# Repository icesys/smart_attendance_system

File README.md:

<h1 align="center">Smart Attendance System</h1>

<p align="center">
  
  <br>
  <sub><i>The finished device: three stacked PCBs.</i></sub>
</p>

<p align="center">
  <b>Embedded systems project</b><br>
  A battery-powered, cable-free device that records lecture attendance when students tap their existing RFID student card.
</p>

<p align="center">
  <a href="#-about">About</a> &nbsp;·&nbsp;
  <a href="#-from-prototype-to-final-device">Build</a> &nbsp;·&nbsp;
  <a href="#-how-it-works">How It Works</a> &nbsp;·&nbsp;
  <a href="#-key-features">Features</a> &nbsp;·&nbsp;
  <a href="#-hardware">Hardware</a> &nbsp;·&nbsp;
  <a href="#-pinout">Pinout</a> &nbsp;·&nbsp;
  <a href="#-firmware">Firmware</a> &nbsp;·&nbsp;
  <a href="#-documentation">Documentation</a> &nbsp;·&nbsp;
  <a href="#-repository-structure">Structure</a> &nbsp;·&nbsp;
  <a href="#-roadmap">Roadmap</a>
</p>

---

<h2>📌 About</h2>

Attendance in lecture halls is still often taken on a sheet of paper. That wastes time, invites mistakes and fraud (signing for an absent friend), and the data has to be typed in again afterwards.

Every student already carries a **student card with an RFID chip**, used daily at the student restaurant: you lay it flat on a small reader and the visit is recorded. We (**Evidence Tsongodza** and **Langelihle Sasha Mandebvu**) built **Smart Attendance System** to bring the same gesture to lectures. At the end of the session the lecturer stands at the door with the device, and each student taps their card on the way out. The device identifies the student, time-stamps the tap, ignores repeated taps and saves everything to a microSD card. Afterwards the lecturer plugs it into a PC, where the card appears as a **USB drive** holding ready-to-use CSV files.

> [!NOTE]
> Status: **complete.** The three PCBs are built and assembled, and the device passed all eight system tests (T1 to T8).

---

<h2>📸 From Prototype to Final Device</h2>

<table>
  <tr>
    <td align="center" width="50%"><br><b>Breadboard prototype</b></td>
    <td align="center" width="50%"><br><b>Final device reading a card</b></td>
  </tr>
</table>

---

<h2>🔄 How It Works</h2>

1. The lecturer switches the device on (the blue LED blinks twice every 3 s) and presses **button 1** to start a session.
2. Each student lays their card flat on the **TAP CARD** area (125 kHz field).
3. The RDM6300 reader sends the card UID to the ESP32-S3, which checks the frame, looks the UID up in `students.csv`, reads the time from the DS3231 clock and appends a line to the session file.
4. LEDs, buzzer and OLED show the result straight away: **present**, **unknown card**, **duplicate** or **error**.
5. A long press on button 1 ends the session and writes a final list sorted by surname.
6. After the lecture, plugging the native USB-C port into a PC shows the microSD card as a USB drive.

No cable is needed during the lecture: the device runs on an 18650 battery charged over USB-C.

---

<h2>⚡ Key Features</h2>

| | Feature | Detail |
|---|---|---|
| 🧠 | **Controller** | ESP32-S3 N16R8 dev board (16 MB flash, 8 MB PSRAM, native USB) |
| 💳 | **Card reading** | RDM6300, 125 kHz EM4100, card laid flat, 14-byte frame checked by XOR checksum |
| 🕒 | **Time stamps** | DS3231 real-time clock with CR2032 backup |
| 💾 | **Storage** | microSD (FAT32): one CSV per session + a sorted final list per session |
| 🖥️ | **PC access** | USB drive mode (automatic when a PC is plugged in) + serial commands |
| 🔁 | **No duplicates** | A card is counted once per session; a card left on the reader is ignored for 1.5 s |
| 👤 | **Student list** | `students.csv` maps each UID to surname, first names and registration number |
| 🔔 | **Feedback** | 3 LEDs, buzzer (transistor driven), 0.96" OLED |
| 🔋 | **Power** | 18650 cell → TP4056 (USB-C charging + protection) → switch → MT3608 5 V boost |
| 🛠️ | **PCBs** | Three stacked 95 × 60 mm two-layer boards designed in KiCad, joined by two ribbon cables |

---

<h2>💳 Why a 125 kHz Reader?</h2>

The frequency of the student card was not documented. An iPhone (NFC Tools) and an Android phone did not detect the card, while the same Android phone read a passport (13.56 MHz) normally. Phones only read 13.56 MHz, so the card is low frequency (**125 kHz**). The RDM6300 reader then confirmed it.

<h2>🔬 Why ESP32-S3?</h2>

Its **native USB** lets the microSD card appear as a USB drive on the PC with no software to install. It also has enough pins, memory and speed for the reader, clock, card, display and feedback at once. The **dev board is mounted on sockets** instead of designing around the bare chip, which avoids the riskiest part of the board design (antenna, flash, boot circuit).

---

<h2>🏗️ System Architecture</h2>

```mermaid
flowchart LR
    CARD[Student card 125 kHz] -.->|field| COIL[Antenna coil]
    COIL --> RFID[RDM6300 reader]
    RFID -->|UART 9600| MCU[ESP32-S3]
    BTN[2 buttons] -->|GPIO40/41| MCU
    RTC[DS3231 clock] <-->|I2C| MCU
    MCU <-->|SPI| SD[(microSD)]
    MCU -->|I2C| OLED[OLED 0.96in]
    MCU -->|GPIO1/2/5, 42| FB[3 LEDs + buzzer]
    MCU <-->|native USB-C| PC[Lecturer's PC]
    BAT[18650] --> CHG[TP4056] --> SW[Switch] --> BOOST[MT3608 5 V] --> D[Schottky] -->|5V_SYS| MCU
```

---

<h2>🔧 Hardware</h2>

The circuit is split over **three stacked 95 × 60 mm boards** to keep the device hand-sized:

| Board | Contents |
|---|---|
| **TOP** | OLED, blue/green/red LEDs, 2 buttons, buzzer + 2N2222A, RFID coil area (no copper) |
| **MIDDLE** | ESP32-S3 on 2 × 22 sockets, RDM6300, Schottky diode, decoupling |
| **BOTTOM** | 18650 holder (underneath), TP4056, slide switch, MT3608, 470 µF, microSD, DS3231 |

Cable 1 joins TOP J1 ↔ MIDDLE J105; cable 2 joins MIDDLE J106 ↔ BOTTOM J201. Both are 16-wire ribbons with the same pin number at both ends.

**Power path:** 18650 → TP4056 → switch → MT3608 (set to **5.0 V with a multimeter before connecting anything**) → Schottky → 5V_SYS (ESP32 5V pin, RDM6300, microSD). 3V3 comes from the ESP32 board regulator (OLED, DS3231, LEDs, buzzer).

> [!WARNING]
> On the protected TP4056, **B− is not ground**: it sits behind the protection transistors. The system ground is **OUT−**. Remove the charging resistor of the DS3231 module: the CR2032 is not rechargeable.

**KiCad projects** (all in `hardware/schematics/kicad/`):

| Project | What it is |
|---|---|
| `sas_complete/` | **The whole system as one circuit**: modules as named-pin blocks, no board connectors (A3) |
| `sas_full_system/` | The three boards and both ribbon cables on one A1 sheet |
| `sas_schematics/` | One sheet per board (hierarchical), shared symbol and footprint libraries |
| `sas_pcb/` | The three routed PCBs, BOM, connector table, power notes, 1:1 printouts |

Gerber and drill files for manufacturing are in `hardware/gerbers/` (one folder per board; zip each folder to upload it). The schematic nets match the routed PCBs (29 nets, identical). Datasheets of every chip and module are in `hardware/datasheets/`.

---

<h2>🔌 Pinout</h2>

| ESP32-S3 GPIO | Connected to | Bus |
|---|---|---|
| 1 / 2 / 5 | Green / red / blue LED (220 Ω) | output |
| 42 | Buzzer transistor base (1 kΩ) | output |
| 40 / 41 | Button 1 (session) / button 2 (info) | input, pull-up |
| 8 / 9 | SCL / SDA: OLED 0x3C, DS3231 0x68 | I2C |
| 10 / 11 / 12 / 13 | microSD CS / SCK / MOSI / MISO | SPI |
| 18 | RDM6300 TX | UART1, 9600 baud |

All pins and options live in [`firmware/include/config.h`](firmware/include/config.h).

---

<h2>🎯 Device Feedback</h2>

| Event | LED | Buzzer |
|---|---|---|
| Start-up OK | green × 3 | 3 beeps |
| Student present | green | 1 short beep |
| Unknown card | red | 1 long beep |
| Duplicate tap | red × 2 | 2 beeps |
| No session running | red × 2 | 2 beeps |
| Session started / ended | green × 3 / red × 2 (long) | 3 beeps / 2 long beeps |
| Error (SD card, clock) | red × 3 | 3 beeps |
| System on | blue: 2 blinks every 3 s | — |

---

<h2>💾 Firmware</h2>

PlatformIO project (Arduino framework) in [`firmware/`](firmware/):

| File | Content |
|---|---|
| `src/main.cpp` | Main program: sessions, card handling, LED/buzzer patterns, OLED, USB drive mode, serial commands |
| `include/config.h` | Every pin, timing and option in one place |
| `include/parsers.h` | Plain C++ helpers (RDM6300 frames, CSV lines, sorting), testable on a PC |
| `test/host/test_parsers.cpp` | 26 unit tests for `parsers.h` (run on the PC) |
| `sketches/D1 … D9` | Step-by-step hardware tests: serial, I2C scan, clock, microSD, reader, LEDs/buzzer/buttons, card read, OLED, clock diagnosis |
| `tools/set_clock.py` | Sets the DS3231 to the PC time over the serial port |
| `data/students.csv` | Template of the student list to copy to the microSD card |

**Files on the microSD card**

| Path | Content |
|---|---|
| `/students.csv` | `UID,Surname,Names,Matricule`, one student per line |
| `/attendance/YYYYMMDD_hhmmss.csv` | One file per session: `uid,surname,names,matricule,date,time,result` |
| `/final/YYYYMMDD_hhmmss.txt` | Final list of the session, sorted by surname, tab-separated (paste into Excel) |

**Build and flash**

```bash
cd firmware
pio run                # build (env: esp32-s3-n16r8)
pio run -t upload      # flash
pio device monitor     # serial monitor, 115200 baud, then type HELP
g++ -std=c++17 -Iinclude test/host/test_parsers.cpp -o t && ./t    # unit tests on the PC
```

<details>
<summary><b>Serial commands</b></summary>
<br>

| Command | Action |
|---|---|
| `HELP` | List the commands |
| `STATUS` | Clock, SD card, students, session |
| `TIME` / `SETTIME YYYY-MM-DD HH:MM:SS` | Show / set the clock |
| `START` / `STOP` | Start or stop a session |
| `LIST`, `DUMP <file>` | List the files / print one |
| `FINAL [file]` | Build and show the sorted final list |
| `STUDENTS`, `RELOAD` | Show / reload the student list |
| `INIT` | Restart the SD card after a problem |
| `MUTE` | Mute or unmute the buzzer |
| `DRIVE` | Show the SD card as a USB drive now |
| `INFO` | Time and count of the last file (same as button 2) |
| `REBOOT` | Restart (also leaves drive mode) |

</details>

<details>
<summary><b>Upload notes</b></summary>
<br>

- Drive mode uses the **native** USB-C port (TinyUSB); serial output goes to the **UART** USB-C port.
- If upload fails with "Unable to verify flash chip connection", hold **BOOT** while it says `Connecting...`.
- On Linux, if the port is not found, add your user to the `dialout` group.

</details>

---

<h2>📚 Documentation</h2>

| Document | Content |
|---|---|
| [`documentation/rapport_final/`](documentation/rapport_final/) | **Project report** in French and English (Word + PDF) |
| [`documentation/poster/`](documentation/poster/) | **Exhibition poster**, two A0 sheets joined side by side (French) |
| `documentation/Resume_mini_projet_smart_attendance_system.pdf` | Short project summary (French) |
| `documentation/bill_of_materials.md` | All parts, grouped by function, with board references |
| `documentation/assembly_guide.md` | PCB soldering order, stacking and first power-on |
| `documentation/system_architecture.md` | Blocks, power rails, data flow |
| `documentation/requirements.md`, `decisions_log.md`, `test_plan.md`, `project_plan.md` | Project management documents |
| `simulation/power_budget.md` | Current per part, battery life, charge time (estimates) |
| `hardware/schematics/kicad/sas_pcb/documentation/` | BOM per reference, connector table, power distribution |
| `hardware/datasheets/` | Datasheets of the chips and modules |
| `media/diagrams/` | Block diagram, flowcharts, schematic and PCB images |

---

<h2>🧰 Tools</h2>

| Tool | Used for |
|---|---|
| VS Code + PlatformIO | Firmware |
| KiCad | Schematics and PCBs |
| Python (pyserial) | `set_clock.py` (sets the clock from the PC) |
| Word / LibreOffice | Project report |

---

<h2>📁 Repository Structure</h2>

| Path | Content |
|---|---|
| `documentation/` | Final report (FR/EN), poster, BOM, assembly guide, requirements, decisions log, test plan |
| `firmware/` | PlatformIO project for the ESP32-S3 |
| `hardware/schematics/kicad/` | KiCad projects: `sas_complete`, `sas_full_system`, `sas_schematics`, `sas_pcb` |
| `hardware/gerbers/` | Gerber and drill files of the three boards |
| `hardware/datasheets/` | Datasheets |
| `simulation/` | Calculations (power budget, battery life) |
| `media/` | Photos of the device and diagrams |

---

<h2>💡 Lessons Learned</h2>

- **Identify before you buy:** two phones were enough to rule out 13.56 MHz, so only one reader type had to be bought.
- **Prototype module by module:** the D1–D9 test sketches made every fault easy to locate before the full firmware ran.
- **Keep the PCB scope realistic:** the ESP32-S3 dev board on sockets and ready-made modules removed the hardest parts of the design.
- **Print 1:1 before ordering:** hand-measured module footprints were checked by laying the real modules on a paper printout.
- **Battery modules have traps:** B− of a protected TP4056 is not ground, and the DS3231 module charges its coin cell unless its resistor is removed.
- **Never share a card between two writers:** in USB drive mode the PC owns the microSD; the firmware restarts afterwards to read it cleanly.
- **Solid-core wire beats jumpers:** 22 AWG wire in red/black/green made the breadboard far more reliable than Dupont jumpers.

---

<h2>⚠️ Limitations</h2>

- A 125 kHz card UID is a plain number that can be copied, and a student could tap a friend's card. The system proves that a **card** was tapped, not that its owner was present.
- Only 125 kHz (EM4100) cards are read, at about 3 cm.
- The time from tap to beep is about 1–2 s, slower than the 1 s target.
- The student list must be prepared and copied to the microSD card by the lecturer.

---

<h2>🗺️ Roadmap</h2>

- [x] Concept, requirements and decisions log
- [x] Breadboard prototype and first card read (125 kHz confirmed)
- [x] Firmware: read, time-stamp, store, no duplicates, student list, final list, USB drive mode, OLED
- [x] Unit tests of the parsers (26 passing)
- [x] KiCad schematics (per board, three boards with cables, whole system as one circuit)
- [x] Three PCBs placed, routed and checked; Gerber files generated
- [x] Project report (French and English) with test results
- [x] Exhibition poster
- [x] PCB manufacturing and assembly
- [x] Full test plan on the real boards (T1 to T8)

**Possible future work:** 3D-printed enclosure, battery level display, Wi-Fi upload, dual-frequency reader.

---

<h1 align="center">DISCLAIMER</h1>
<h4 align="center">Embedded systems project. It records card taps only and is not a secure identity verification system.</h4>

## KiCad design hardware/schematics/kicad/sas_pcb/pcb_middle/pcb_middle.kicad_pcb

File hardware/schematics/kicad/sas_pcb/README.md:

# sas_pcb: the three routed boards

Open the `.kicad_pro` of the board you want (KiCad 10):

| Project | Board | Parts | Track segments / vias |
|---|---|---|---|
| `pcb_top/pcb_top.kicad_pro` | TOP 95 × 60 mm: OLED, LEDs, buttons, buzzer, RFID coil area | 20 + 4 M3 holes | 245 / 21 |
| `pcb_middle/pcb_middle.kicad_pro` | MIDDLE 95 × 60 mm: ESP32-S3 sockets, RDM6300, Schottky diode | 9 + 4 M3 holes | 343 / 45 |
| `pcb_bottom/pcb_bottom.kicad_pro` | BOTTOM 95 × 60 mm: TP4056, switch, MT3608, microSD, DS3231 | 9 + 4 M3 holes | 180 / 23 |

| Folder / file | Content |
|---|---|
| `smart_attendance.pretty/` | All footprints used: 8 module footprints drawn from caliper measurements + copies of the standard ones |
| `sas_symbols.kicad_sym` | All symbols used |
| `documentation/BOM.csv` | Bill of materials per reference |
| `documentation/Connector_Table.md` | Pinout of both ribbon cables |
| `documentation/Power_Distribution.md` | Power path, rails, track widths |
| `printouts_1to1/` | 1:1 PDFs to check the module footprints with the real modules |

Gerber and drill files: `../../../gerbers/`.

## Layout
- M3 holes (3.2 mm) at (4,4), (91,4), (4,56), (91,56) mm on all boards.
- Cable 1 (TOP J1 = MIDDLE J105) at (87.95, 26.5); cable 2 (MIDDLE J106 = BOTTOM J201) at (25.29, 44.75), same orientation on both boards of a pair.
- TOP: RFID coil area x 8–54, y 22–57 mm is a keep-out (no tracks, vias or copper).
- MIDDLE: the ESP32-S3 USB-C ports face the left edge.
- BOTTOM: TP4056 USB-C against the top edge; battery holder under the board, wired to J202.

## Design rules
2 copper layers, 1.6 mm. Clearance 0.3 mm. Tracks: signals 0.3 mm, GND 0.4, 3V3 0.5, 5V_SYS 0.6, 5V_BOOST 0.8, BAT+, BAT−, CHG_OUT+, SW_OUT 1.0 mm. Vias 0.8 mm pad / 0.4 mm drill. Copper at least 0.55 mm from the board edge. Every net, GND included, is connected by tracks; GND also has a copper pour on both layers with solid pad connections.

## Checks
- Every pad on the net of the schematic (0 mismatches); 29 nets, identical to the schematics.
- DRC in KiCad 10: 0 unconnected items on all three boards.
- Footprints checked by laying the real modules on the 1:1 printouts.

Before re-plotting the Gerbers after any change: press **B** (Edit > Fill All Zones), run **Inspect > Design Rules Checker**, then **File > Fabrication Outputs**.

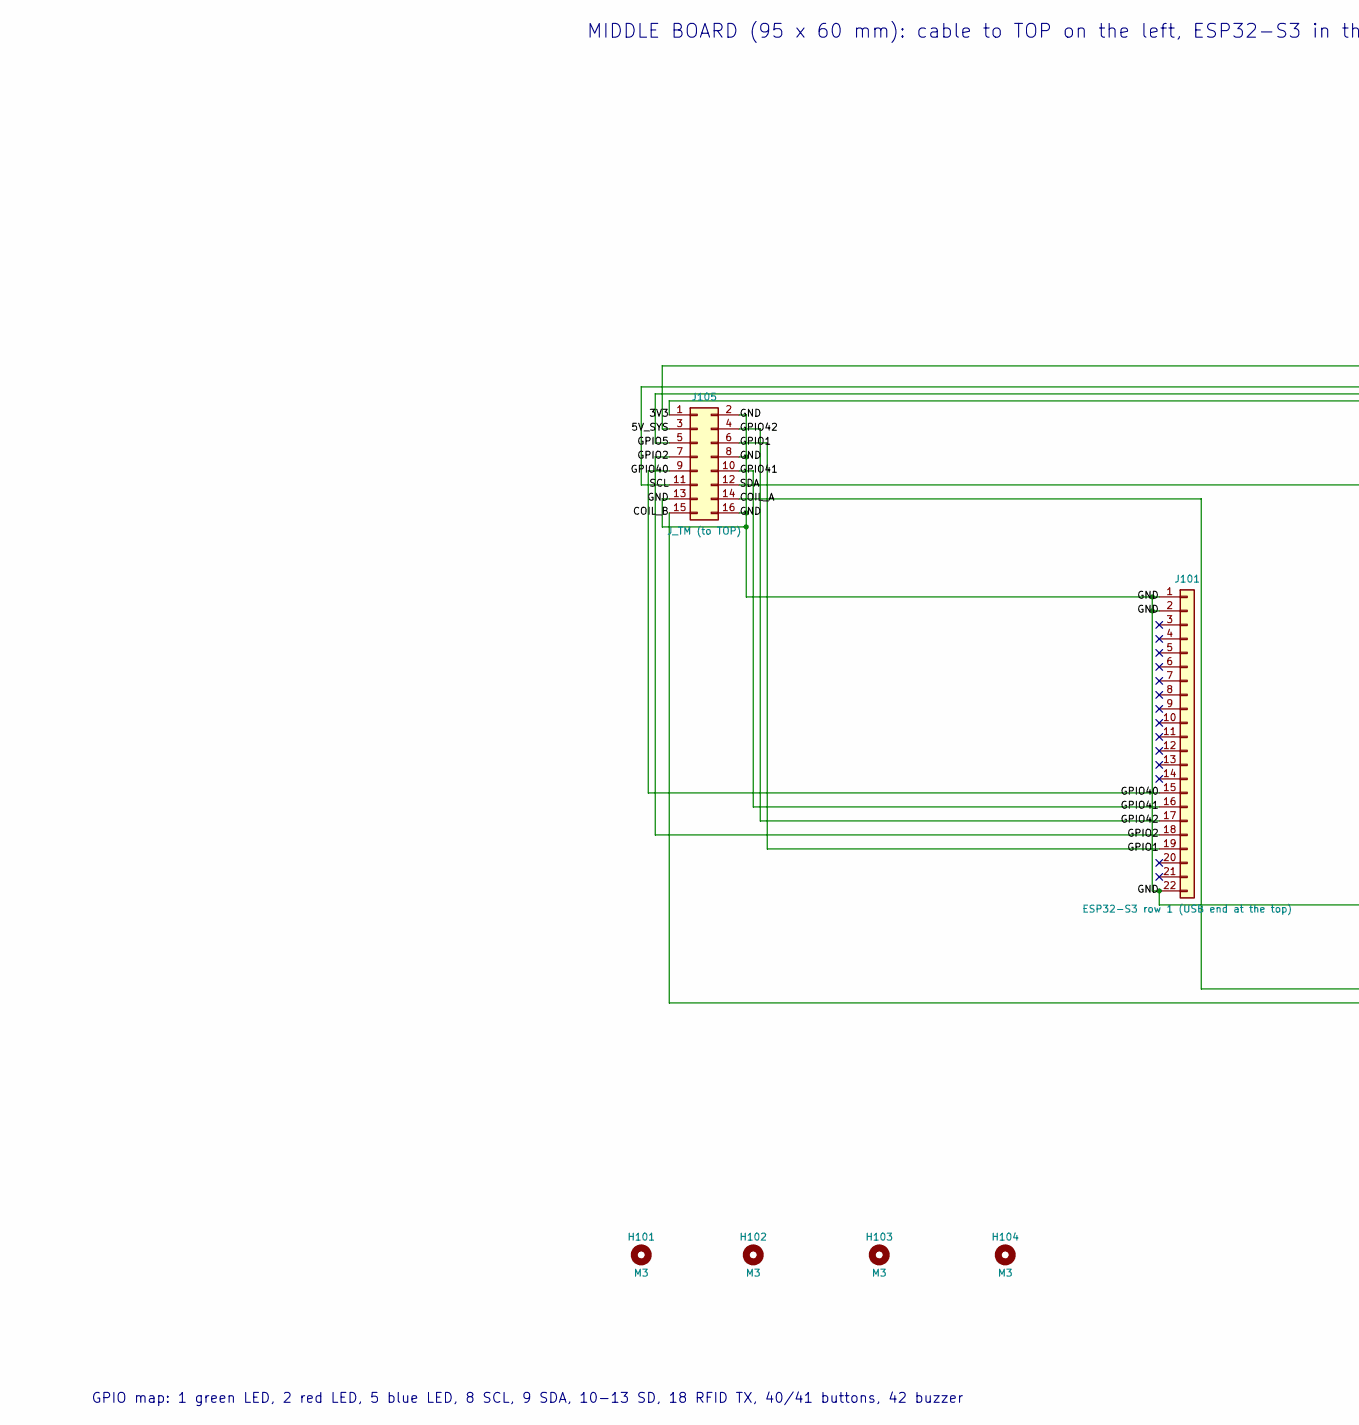
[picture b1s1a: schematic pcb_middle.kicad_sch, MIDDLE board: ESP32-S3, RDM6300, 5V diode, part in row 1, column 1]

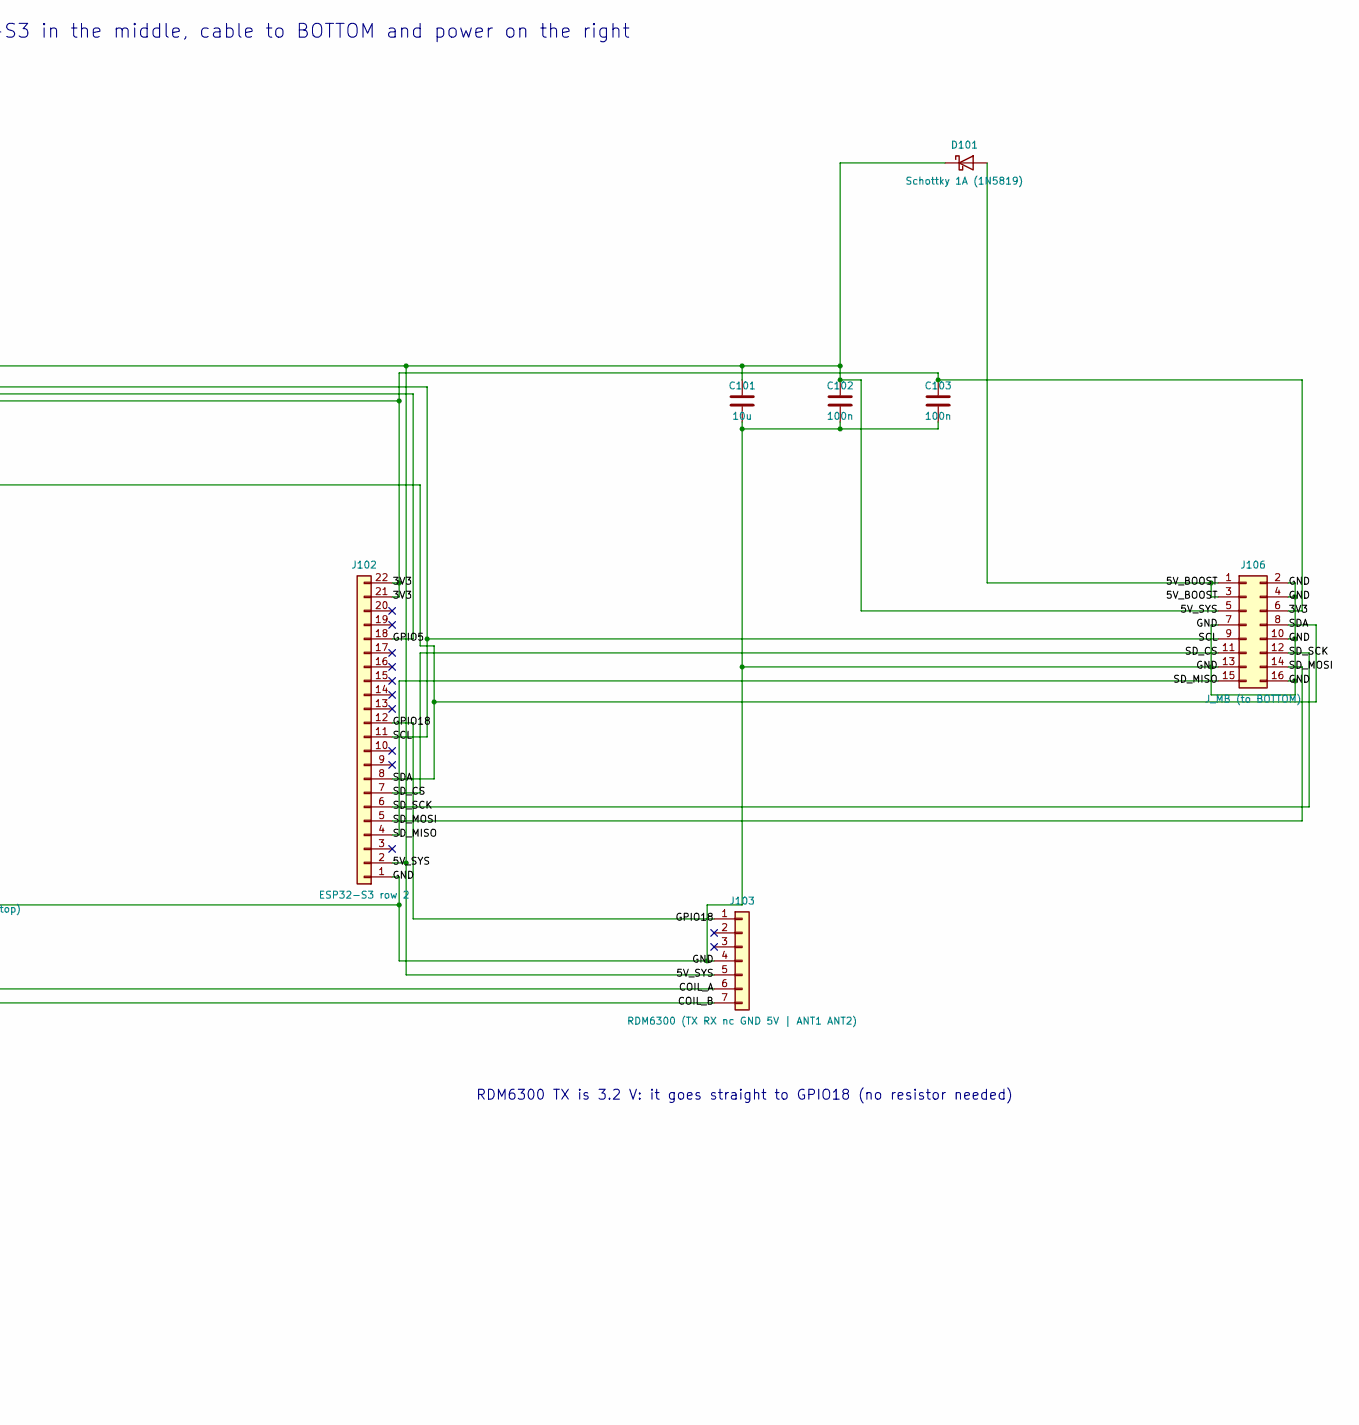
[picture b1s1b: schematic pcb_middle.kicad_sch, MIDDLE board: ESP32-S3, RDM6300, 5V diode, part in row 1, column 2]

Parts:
C101: 10u; C_Disc_D5.0mm_W2.5mm_P5.00mm
C102, C103: 100n; C_Disc_D5.0mm_W2.5mm_P5.00mm
D101: Schottky 1A (1N5819); D_DO-41_SOD81_P10.16mm_Horizontal
H101, H102, H103, H104: M3; MountingHole_3.2mm_M3
J101: ESP32-S3 row 1 (USB end at the top); PinSocket_1x22_P2.54mm_Vertical
J102: ESP32-S3 row 2; PinSocket_1x22_P2.54mm_Vertical
J103: RDM6300 (TX RX nc GND 5V | ANT1 ANT2); MOD_RDM6300
J105: J_TM (to TOP); IDC-Header_2x08_P2.54mm_Vertical
J106: J_MB (to BOTTOM); IDC-Header_2x08_P2.54mm_Vertical

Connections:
/3V3: C103.1, J102.21, J102.22, J105.1, J106.6
/5V_BOOST: D101.2 (A), J106.1, J106.3
/5V_SYS: C101.1, C102.1, D101.1 (K), J102.2, J103.5, J105.3, J106.5
/COIL_A: J103.6, J105.14
/COIL_B: J103.7, J105.15
/GND: C101.2, C102.2, C103.2, J101.1, J101.2, J101.22, J102.1, J103.4, J105.2, J105.8, J105.13, J105.16, J106.2, J106.4, J106.7, J106.10, J106.13, J106.16
/GPIO1: J101.19, J105.6
/GPIO2: J101.18, J105.7
/GPIO5: J102.18, J105.5
/GPIO18: J102.12, J103.1
/GPIO40: J101.15, J105.9
/GPIO41: J101.16, J105.10
/GPIO42: J101.17, J105.4
/SCL: J102.11, J105.11, J106.9
/SDA: J102.8, J105.12, J106.8
/SD_CS: J102.7, J106.11
/SD_MISO: J102.4, J106.15
/SD_MOSI: J102.5, J106.14
/SD_SCK: J102.6, J106.12

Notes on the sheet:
RDM6300 TX is 3.2 V: it goes straight to GPIO18 (no resistor needed)
MIDDLE BOARD (95 x 60 mm): cable to TOP on the left, ESP32-S3 in the middle, cable to BOTTOM and power on the right
GPIO map: 1 green LED, 2 red LED, 5 blue LED, 8 SCL, 9 SDA, 10-13 SD, 18 RFID TX, 40/41 buttons, 42 buzzer

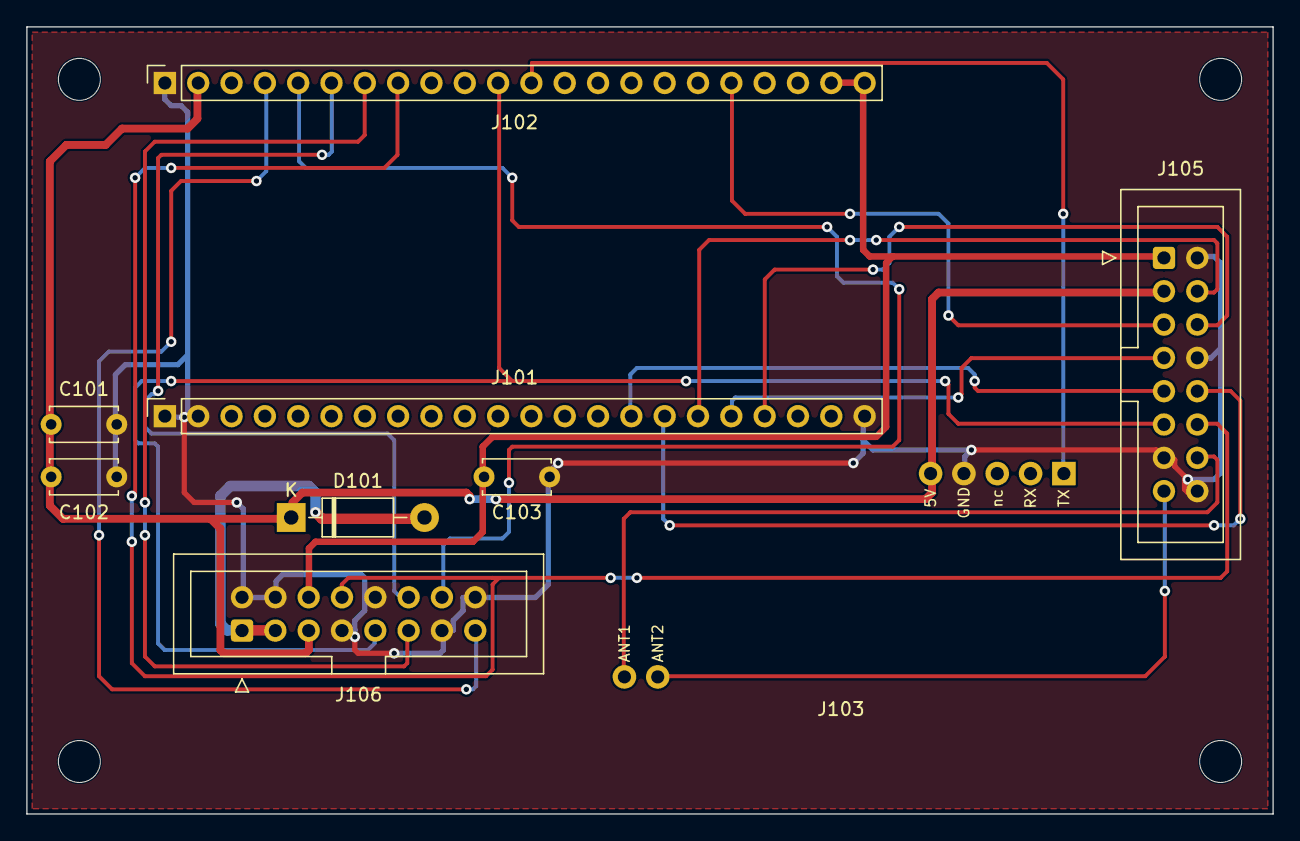
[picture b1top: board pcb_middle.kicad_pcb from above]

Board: 2 copper layers, 95.0 x 60.0 mm, 13 parts (0 on the bottom side), 19 nets.

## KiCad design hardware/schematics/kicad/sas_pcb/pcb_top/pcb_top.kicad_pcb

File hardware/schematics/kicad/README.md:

# sas_schematics: Smart Attendance System, electrical schematics (v0.6)

Open `sas_schematics.kicad_pro` in KiCad 7 or newer (tested here with 7.0.11; you use 10, which converts the files when you save).
The root sheet shows the three boards; double-click a box to open it.

| Sheet | File | References |
|---|---|---|
| TOP | `top.kicad_sch` | 1-99 |
| MIDDLE | `middle.kicad_sch` | 101-199 |
| BOTTOM | `bottom.kicad_sch` | 201-299 |

The sheets are separate boards: nothing joins them inside KiCad. The two ribbon cables use the same pin numbers at both ends (TOP J1 = MIDDLE J105, MIDDLE J106 = BOTTOM J201); the pinouts are listed on the root sheet.

## Libraries in this folder (so it opens the same in any KiCad version)
- `sas_symbols.kicad_sym` (nickname SAS): copies of the standard symbols used. Declared in `sym-lib-table`.
- `smart_attendance.pretty`: the 8 custom module footprints, built from your drawings. Declared in `fp-lib-table`.

## Power path
18650 -> TP4056 (protected, USB-C) -> slide switch -> MT3608 (set to 5.0 V with a multimeter first) -> cable 2 pins 1 and 3 (5V_BOOST) -> MIDDLE Schottky diode -> 5V_SYS (ESP32 5V pin, RDM6300, SD module, buzzer option). 3V3 comes from the ESP32 board. BAT- is not ground (OUT- is). On battery the board sits at about 4.7 V; USB (about 5 V) takes over when plugged in.

## Footprint orientation rule
Header-mounted modules (OLED, SD, DS3231, RDM6300) plug in pin-down, so each footprint is the MIRROR of your hand drawing (which shows the face the pin tips point to). TP4056 and MT3608 are drawn component-side up as in your drawings. **Check with a 1:1 print before ordering**: put the real module upside-down on the printout; every pin must land on the pad with the same name.

## What was verified (KiCad 7.0.11 command line)
- Every net of the wired schematics matches the intended connections exactly (script comparison against the exported netlist); no duplicate references; every footprint name exists.
- Your ERC runs: MIDDLE and BOTTOM 0 errors, 0 warnings. TOP had 5 warnings caused by KiCad 10's library differing from KiCad 7's; they disappear now that the symbols come from `sas_symbols.kicad_sym`. Please run ERC once more.

## Remaining small assumptions (outline only, no electrical effect)
Distance from each header row to the module's top edge (OLED 2.5 mm, SD and DS3231 2.0 mm, RDM6300 1.0 mm), TP4056 pad row 2.0 mm from its bottom edge, buzzer + pin, slide-switch body orientation.

`tools/` holds the generators (`gen_schematics.py`, `gen_footprints.py`).

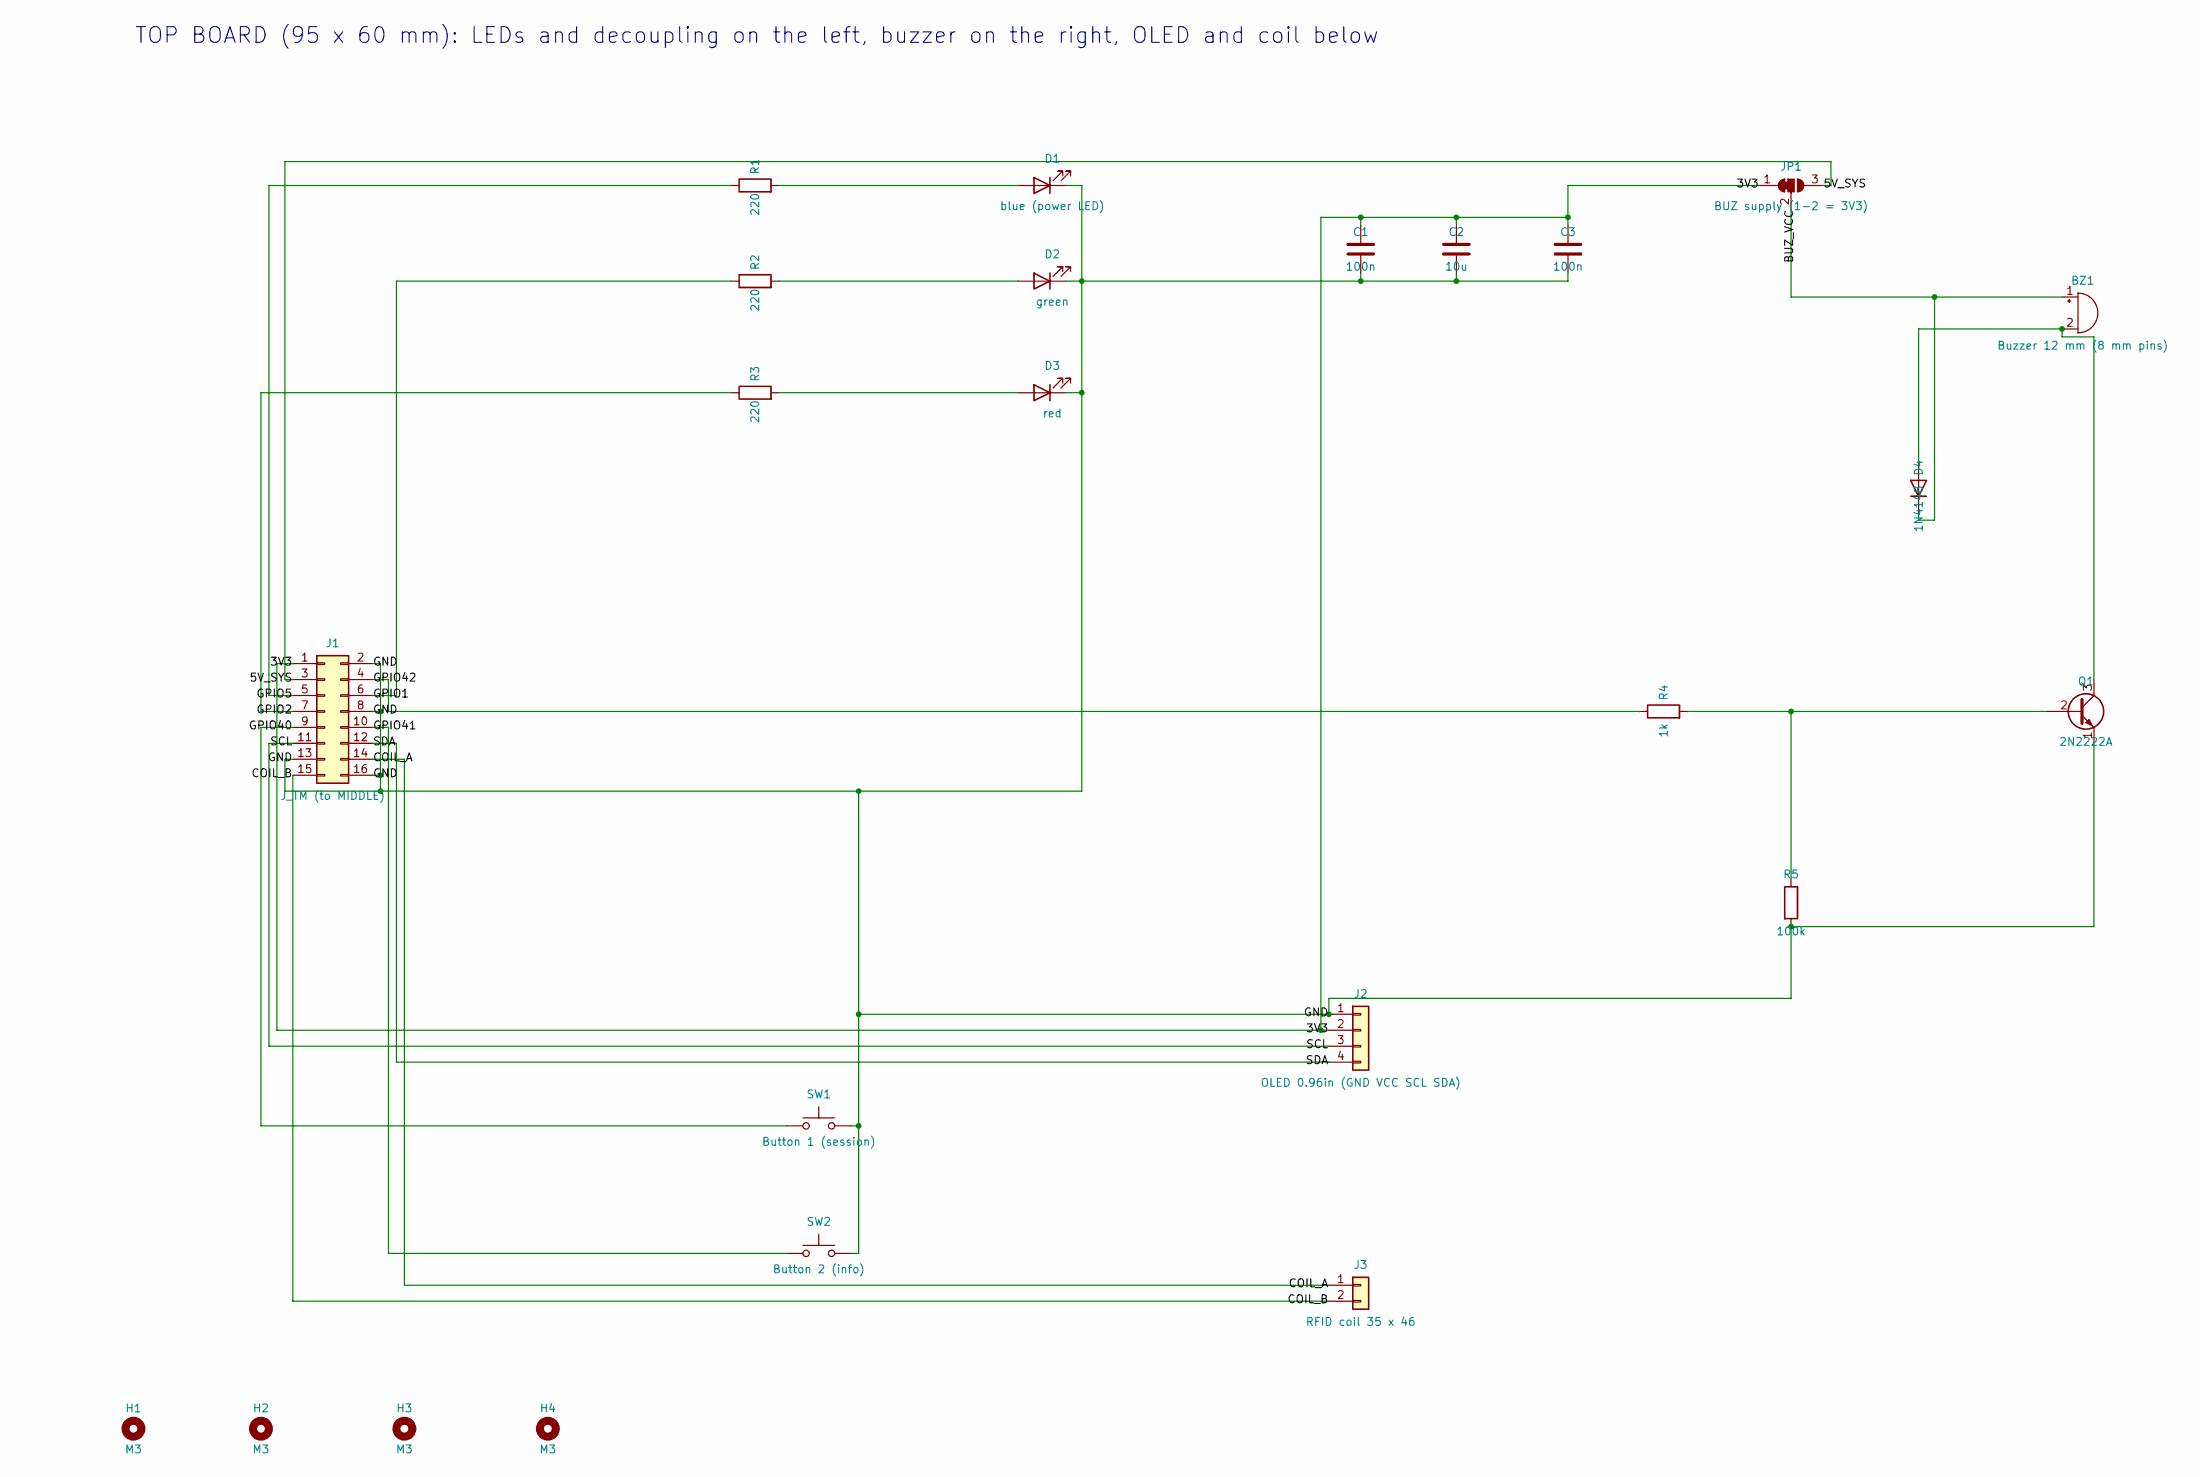
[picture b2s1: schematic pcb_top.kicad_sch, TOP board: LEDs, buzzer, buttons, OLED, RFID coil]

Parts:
BZ1: Buzzer 12 mm (8 mm pins); Buzzer_12mm_P8mm
C1, C3: 100n; C_Disc_D5.0mm_W2.5mm_P5.00mm
C2: 10u; C_Disc_D5.0mm_W2.5mm_P5.00mm
D1: blue (power LED); LED_D5.0mm
D2: green; LED_D5.0mm
D3: red; LED_D5.0mm
D4: 1N4148; D_DO-35_SOD27_P7.62mm_Horizontal
H1, H2, H3, H4: M3; MountingHole_3.2mm_M3
J1: J_TM (to MIDDLE); IDC-Header_2x08_P2.54mm_Vertical
J2: OLED 0.96in (GND VCC SCL SDA); MOD_OLED096
J3: RFID coil 35 x 46; PinHeader_1x02_P2.54mm_Vertical
JP1: BUZ supply (1-2 = 3V3); SolderJumper-3_P1.3mm_Bridged12_RoundedPad1.0x1.5mm
Q1: 2N2222A; TO-92_Inline
R1, R2, R3: 220; R_Axial_DIN0207_L6.3mm_D2.5mm_P7.62mm_Horizontal
R4: 1k; R_Axial_DIN0207_L6.3mm_D2.5mm_P7.62mm_Horizontal
R5: 100k; R_Axial_DIN0207_L6.3mm_D2.5mm_P7.62mm_Horizontal
SW1: Button 1 (session); SW_PUSH_6mm
SW2: Button 2 (info); SW_PUSH_6mm

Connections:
/3V3: C1.1, C2.1, C3.1, J1.1, J2.2, JP1.1 (A)
/5V_SYS: J1.3, JP1.3 (B)
/BUZ_VCC: BZ1.1 (+), D4.1 (K), JP1.2 (C)
/COIL_A: J1.14, J3.1
/COIL_B: J1.15, J3.2
/GND: C1.2, C2.2, C3.2, D1.1 (K), D2.1 (K), D3.1 (K), J1.2, J1.8, J1.13, J1.16, J2.1, Q1.1 (E), R5.2, SW1.2, SW2.2
/GPIO1: J1.6, R2.1
/GPIO2: J1.7, R3.1
/GPIO5: J1.5, R1.1
/GPIO40: J1.9, SW1.1
/GPIO41: J1.10, SW2.1
/GPIO42: J1.4, R4.1
/SCL: J1.11, J2.3
/SDA: J1.12, J2.4
unnamed: BZ1.2 (-), D4.2 (A), Q1.3 (C)
unnamed: D1.2 (A), R1.2
unnamed: D2.2 (A), R2.2
unnamed: D3.2 (A), R3.2
unnamed: Q1.2 (B), R4.2, R5.1

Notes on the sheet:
TOP BOARD (95 x 60 mm): LEDs and decoupling on the left, buzzer on the right, OLED and coil below

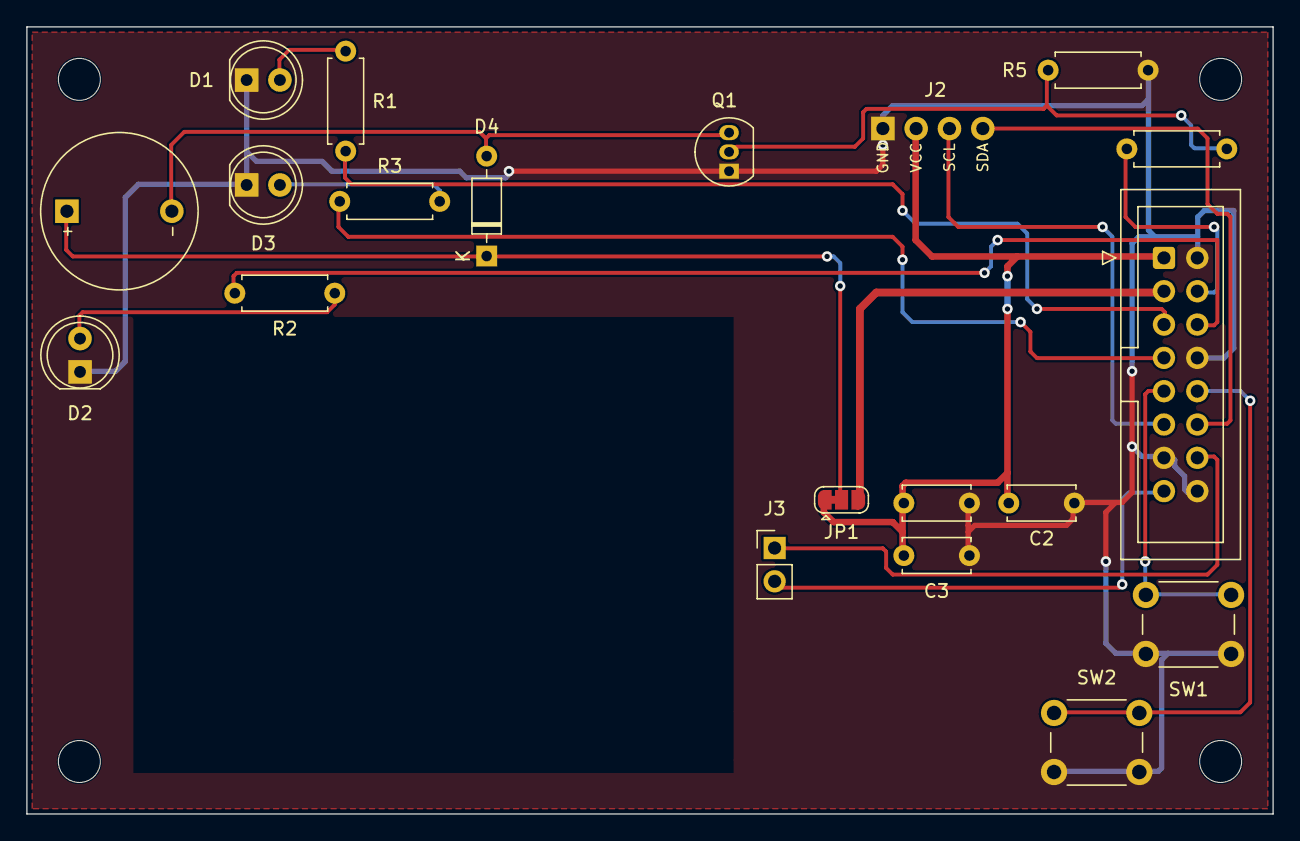
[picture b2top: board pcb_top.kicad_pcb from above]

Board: 2 copper layers, 95.0 x 60.0 mm, 24 parts (0 on the bottom side), 19 nets.

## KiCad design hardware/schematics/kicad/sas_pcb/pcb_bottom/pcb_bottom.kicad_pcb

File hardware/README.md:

# hardware

| Folder | Content |
|---|---|
| [`schematics/kicad/sas_complete/`](schematics/kicad/sas_complete/) | The whole system drawn as one circuit (A3), no board connectors |
| [`schematics/kicad/sas_full_system/`](schematics/kicad/sas_full_system/) | The three boards and both ribbon cables on one A1 sheet |
| [`schematics/kicad/sas_schematics/`](schematics/kicad/sas_schematics/) | One sheet per board (hierarchical), shared symbol and footprint libraries |
| [`schematics/kicad/sas_pcb/`](schematics/kicad/sas_pcb/) | The three routed PCBs, BOM, connector table, power notes, 1:1 printouts |
| [`gerbers/`](gerbers/) | Gerber and drill files of the three boards, one folder per board |
| [`datasheets/`](datasheets/) | Datasheets of the chips and modules |

KiCad 10 (the PCB files are saved in KiCad 10 format). All projects use relative library paths (`${KIPRJMOD}`), so the folder can be moved or cloned anywhere.

## Ordering the PCBs
Zip each folder in `gerbers/` (for example `pcb_top_gerbers_&_drills.zip`) and upload one zip per board. All three boards: 95 × 60 mm, 2 layers, 1.6 mm, HASL, any colour.

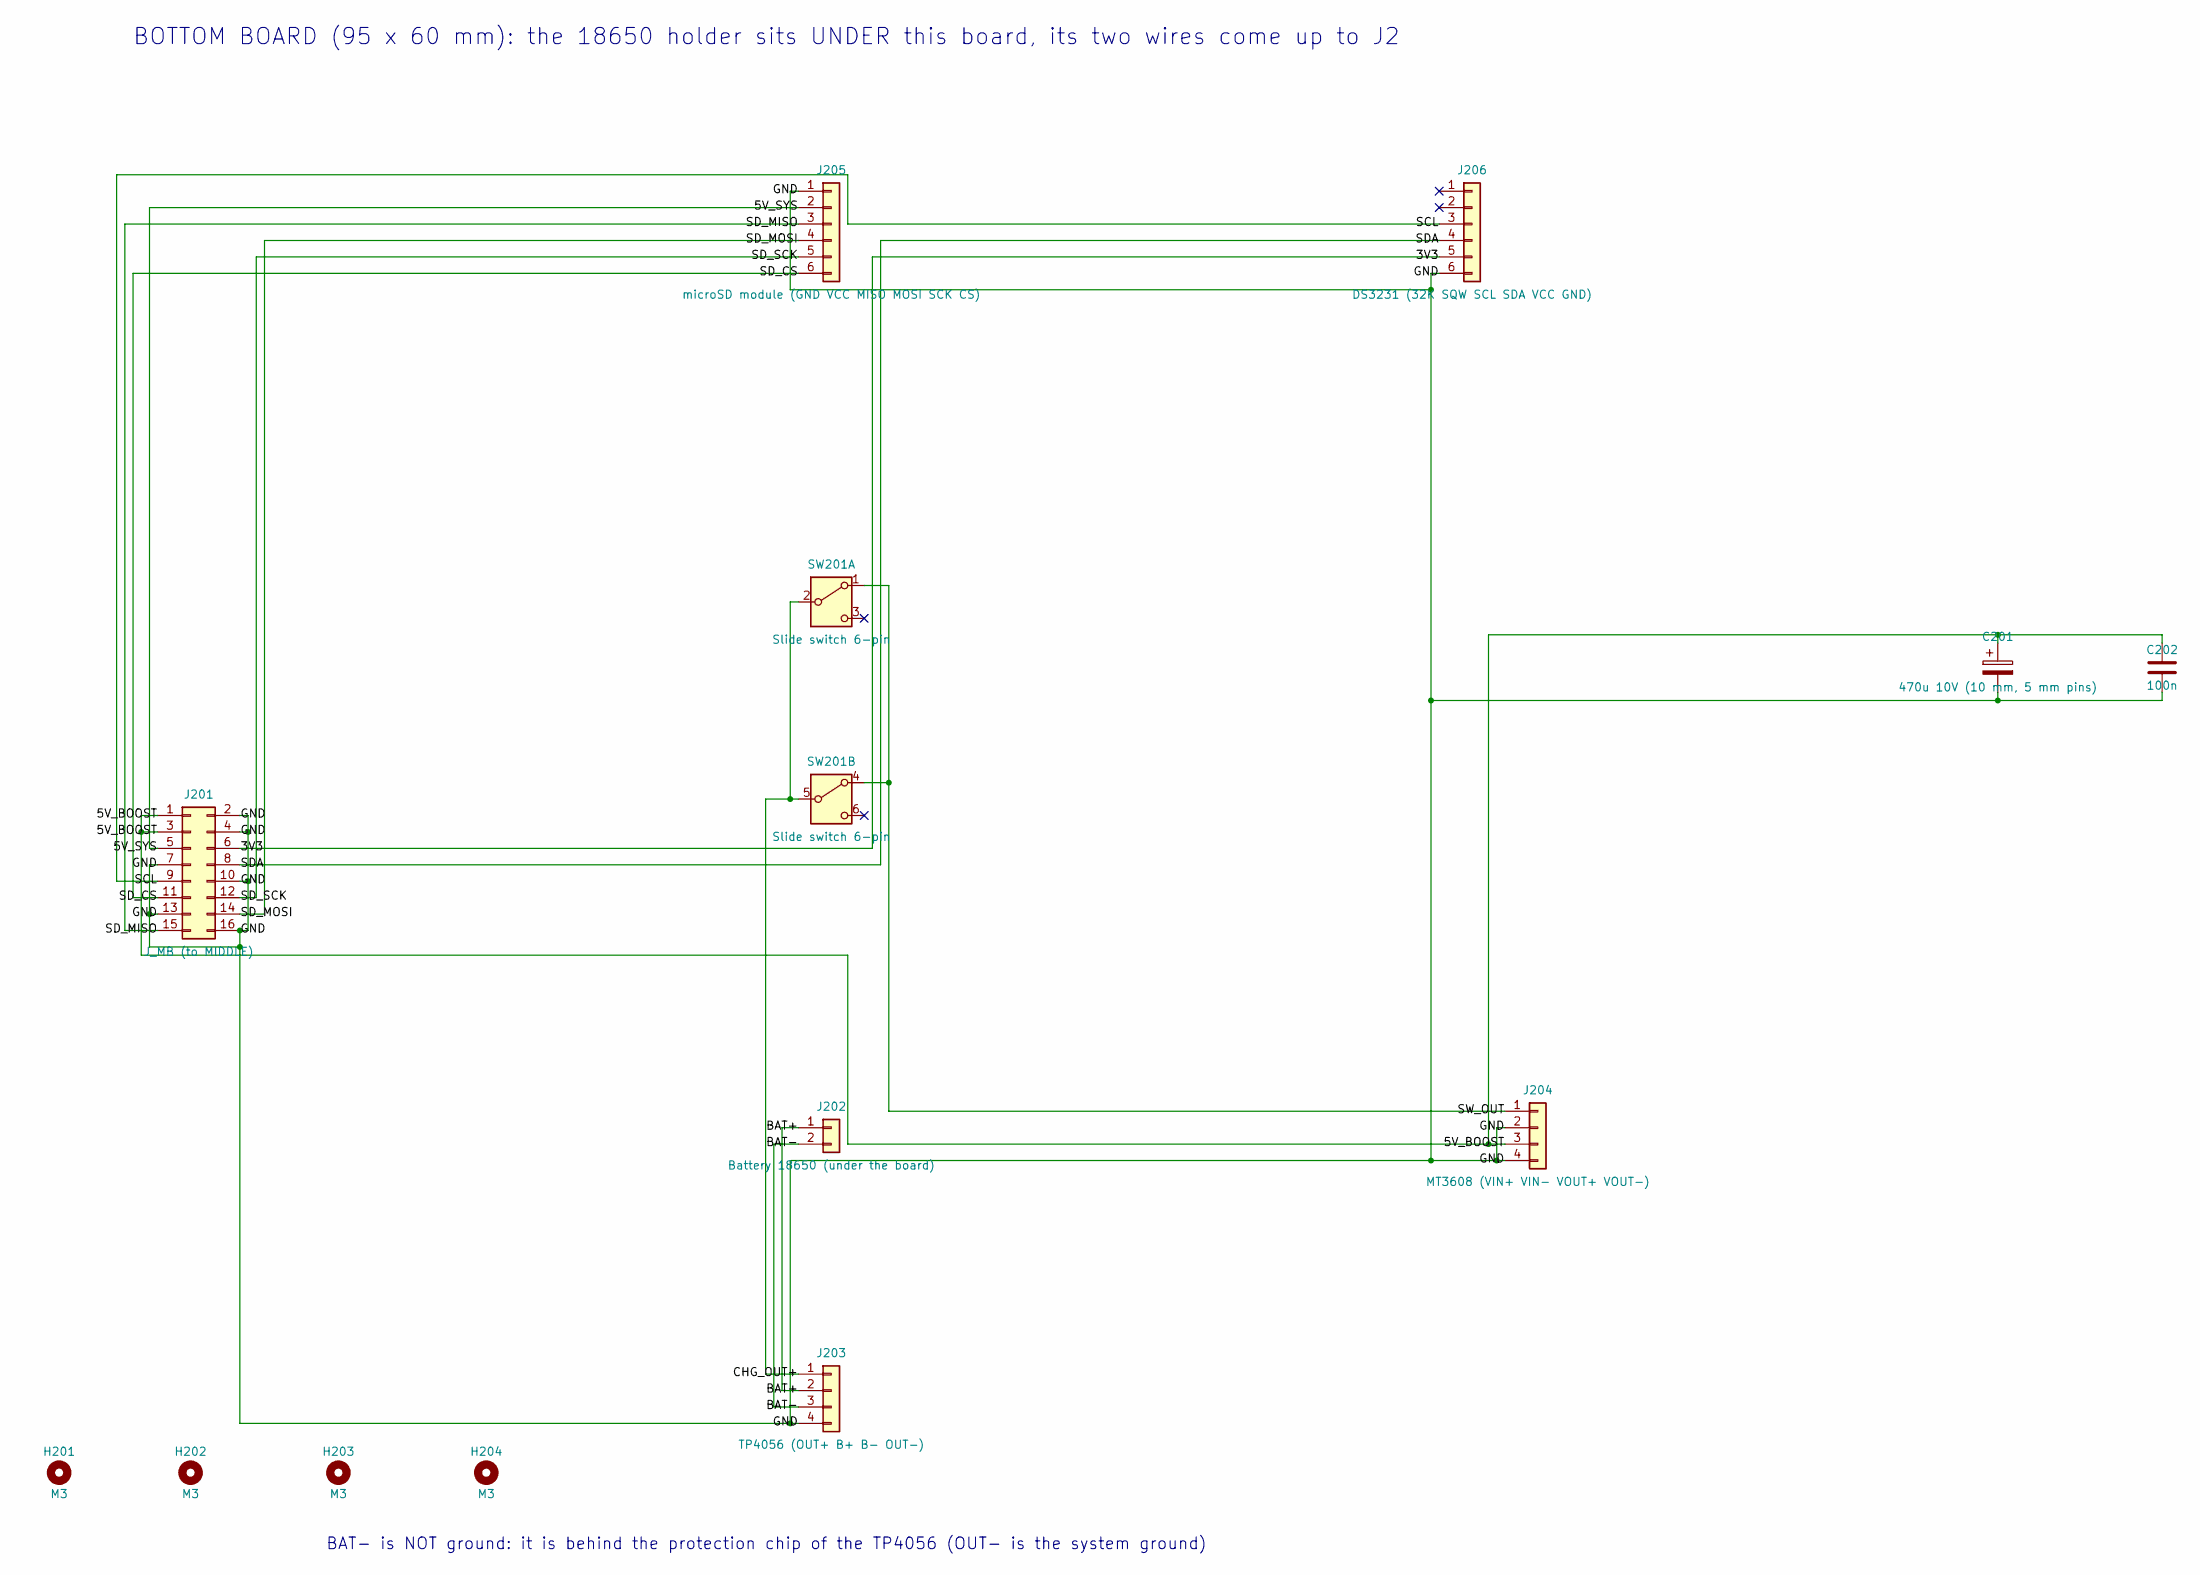
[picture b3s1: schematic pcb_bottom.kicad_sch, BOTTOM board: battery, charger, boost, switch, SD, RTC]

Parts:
C201: 470u 10V (10 mm, 5 mm pins); CP_Radial_D10.0mm_P5.00mm
C202: 100n; C_Disc_D5.0mm_W2.5mm_P5.00mm
H201, H202, H203, H204: M3; MountingHole_3.2mm_M3
J201: J_MB (to MIDDLE); IDC-Header_2x08_P2.54mm_Vertical
J202: Battery 18650 (under the board); PinHeader_1x02_P2.54mm_Vertical
J203: TP4056 (OUT+ B+ B- OUT-); MOD_TP4056
J204: MT3608 (VIN+ VIN- VOUT+ VOUT-); MOD_MT3608
J205: microSD module (GND VCC MISO MOSI SCK CS); MOD_SD_6PIN
J206: DS3231 (32K SQW SCL SDA VCC GND); MOD_DS3231_6PIN
SW201: Slide switch 6-pin; SW_Slide_6pin_2mm

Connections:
/3V3: J201.6, J206.5
/5V_BOOST: C201.1, C202.1, J201.1, J201.3, J204.3
/5V_SYS: J201.5, J205.2
/BAT+: J202.1, J203.2
/BAT-: J202.2, J203.3
/CHG_OUT+: J203.1, SW201.2 (B), SW201.5 (B)
/GND: C201.2, C202.2, J201.2, J201.4, J201.7, J201.10, J201.13, J201.16, J203.4, J204.2, J204.4, J205.1, J206.6
/SCL: J201.9, J206.3
/SDA: J201.8, J206.4
/SD_CS: J201.11, J205.6
/SD_MISO: J201.15, J205.3
/SD_MOSI: J201.14, J205.4
/SD_SCK: J201.12, J205.5
/SW_OUT: J204.1, SW201.1 (A), SW201.4 (A)

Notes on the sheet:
BOTTOM BOARD (95 x 60 mm): the 18650 holder sits UNDER this board, its two wires come up to J2
BAT- is NOT ground: it is behind the protection chip of the TP4056 (OUT- is the system ground)
